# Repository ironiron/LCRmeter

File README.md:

# About

My try at LCR measurment via sinewave and voltage measurment. Generally, it is working, however PCB layout is not great, and ADC is not used optymally, so measuring inductance is more or less futile.
Results are a bit floaty. There is an unpolished oscilloscope mode.

Seems like PCB needs a bit of rerouting.

# Measuring principle. 

See \ref misc folder for more in depth walkthrough. The principle is to measure voltage across known resistor and a DUT.
Since it is sinewave that is used for measurments we can get phase angle, loss angle, etc. 

Now measurment settings (frequency and series resistor), are done manually, but maybe implement automatic one in the future?
eg. if loss angle is small then the capacitance can be calculated with greater accuracy than the ESR. If inductor is to be measured then the measuring frequency should be higher. 

# TODO 

- add under sampling on ADC to increase range of frequency for sinewave
- Add automatic frequency and Rseries adjustment for best possible accuracy.
- reroute PCB
- Add edge detection for oscilloscope mode
- add handling of arbitrary waveform and PWM outputs
- Remove USB stuff - not needed
-

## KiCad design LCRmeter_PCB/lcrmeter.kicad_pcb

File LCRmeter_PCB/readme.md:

# todo

[x] add connector for UART converter for debugging
[x] add testpoint for ADC measurments
[x] make oled from discrete parts, not module
[x] change connector for programmmer, and move it out of the top layer
- check if PCB can be smaller (especially batterry holder)
[x] add more Rseries options
[x] remove option without Rseries connected at all - it can fry PCB
[x] remove connection to 2nd ADCs
[x] Are there  better opamps?? 
[x] remove option for 1.5 V ref
[x] reduce number of caps, and increase its capacitance
[x] think about Rseries diagnosis
[x] make programming interface coherent with stlink or make something with proper connnection
- think about connections to from MCU 
[x] is there MCU with bigger RAM? (no there is none in g4 series)
[] add pulldown for the reset of oled
[] add mounting points for mechanical assembly
- double check connections on schematic

# Decisions background

74LVC1G66 Switches needs to be placed before Rseries so that ADC measurments do no take into account resistance of switches itself.

PCB should be 4 layer to improve EMC. Inner layers should be GND only, VCC is not so critical that needs a power plane.

Capacitors should be 0603 or lower

R series will not have any self diagnosis - too much hassle for little added accuracy

Filters are designed using Analog Devices tool  (https://tools.analog.com/en/filterwizard/)[https://tools.analog.com/en/filterwizard/]
![[media/filters.png]]
Requirments for filter is that 125KHz is a passband with optimally 0 dB ripples and no gain. Alternatively a simple RC filter can be used. Because ADC takes is too invasive for the signal (sampling period is cleary visible on osciloscope), at least internal op-amp is required.

Capacitors for uC are set to larger for same size, in the hope of improving noise performance. There is no simulation done for either option (many little plus one big, vs many bigger), so I do not know if it works, but there is no indication that either is better than other. ST's guidelines seems to be so called tradition of caps of 3 diffferent values.

Copper pour on top and bottom is not allowed, because it can create easi to overlook noisy cavities.

ADCs are on pins that can be mapped thru internal opamp

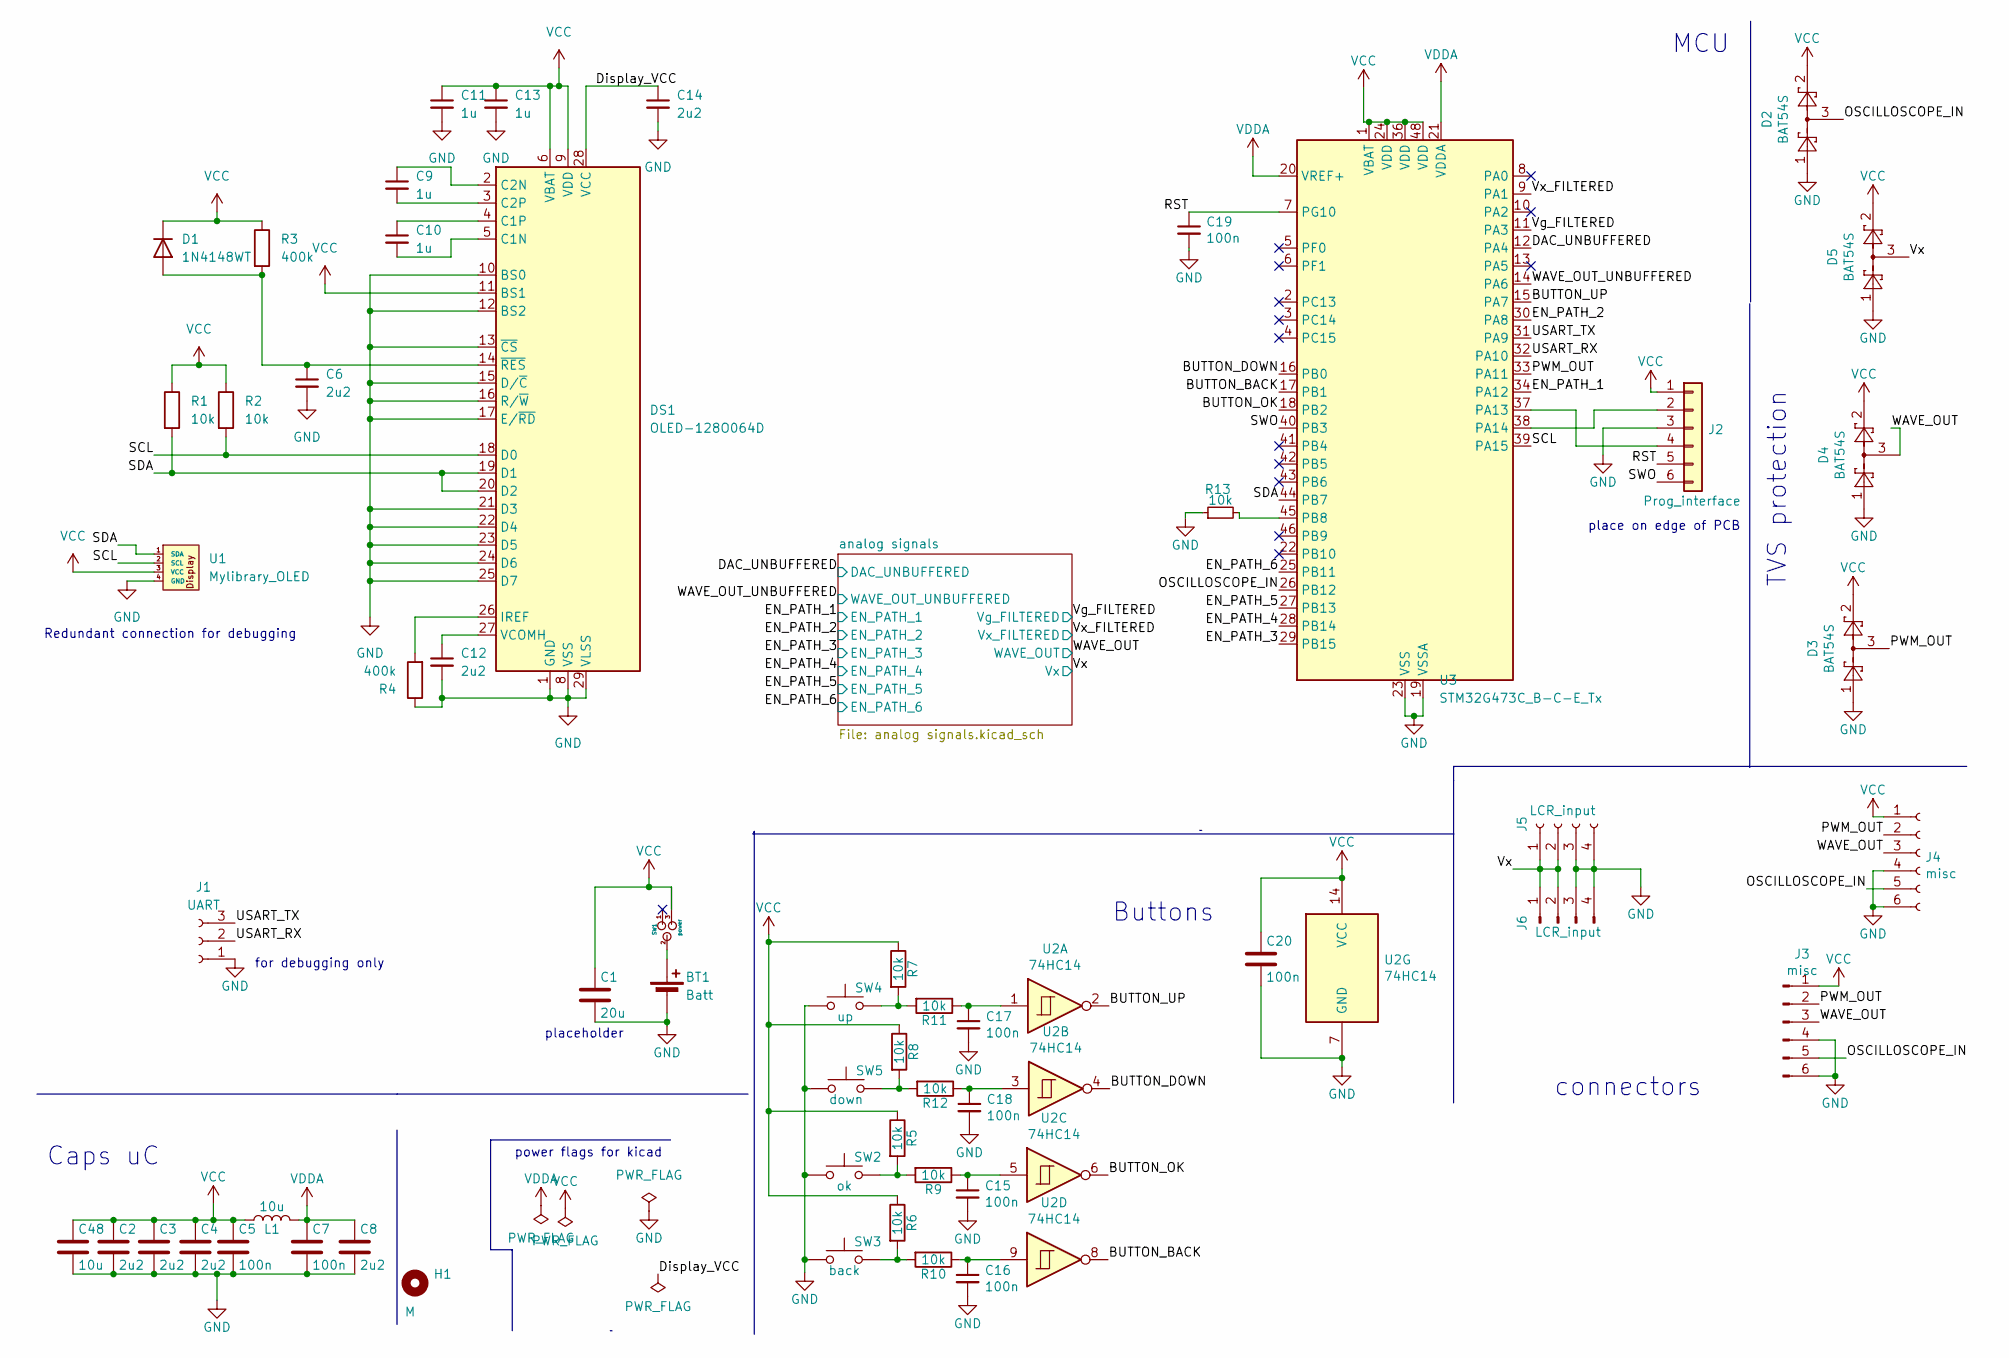
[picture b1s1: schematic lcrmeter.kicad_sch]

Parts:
BT1: Batt; BatteryHolder_Keystone_2468_2xAAA
C1: 20u; C_0805_2012Metric_Pad1.18x1.45mm_HandSolder
C2, C3, C4, C6, C8, C12, C14: 2u2; C_0402_1005Metric_Pad0.74x0.62mm_HandSolder
C5, C7, C15, C16, C17, C18, C19, C20: 100n; C_0402_1005Metric_Pad0.74x0.62mm_HandSolder
C9, C10, C11, C13: 1u; C_0402_1005Metric_Pad0.74x0.62mm_HandSolder
C48: 10u; C_0805_2012Metric_Pad1.18x1.45mm_HandSolder
D1: 1N4148WT; D_SOD-523
D2, D3, D4, D5: BAT54S; SOT-23
DS1: OLED-128O064D
H1: M; MountingHole_3.2mm_M3_ISO14580
J1: UART; Harwin_M20-89003xx_1x03_P2.54mm_Horizontal
J2: Prog_interface; Harwin_M20-89006xx_1x06_P2.54mm_Horizontal
J3: misc; PinSocket_1x06_P2.54mm_Vertical
J4: misc; PinHeader_1x06_P2.54mm_Vertical
J5: LCR_input; PinSocket_1x04_P2.54mm_Vertical
J6: LCR_input; PinHeader_1x04_P2.54mm_Vertical
L1: 10u; L_0805_2012Metric_Pad1.15x1.40mm_HandSolder
R1, R2, R5, R6, R7, R8, R9, R10, R11, R12, R13: 10k; R_0603_1608Metric_Pad0.98x0.95mm_HandSolder
R3, R4: 400k; R_0603_1608Metric_Pad0.98x0.95mm_HandSolder
SW1: power; PinHeader_1x03_P2.54mm_Vertical
SW2: ok; SW_SPST_REED_CT05-XXXX-G1
SW3: back; SW_SPST_REED_CT05-XXXX-G1
SW4: up; SW_SPST_REED_CT05-XXXX-G1
SW5: down; SW_SPST_REED_CT05-XXXX-G1
U1: Mylibrary_OLED; PinHeader_1x04_P2.54mm_Vertical
U2: 74HC14; SOIC-14_3.9x8.7mm_P1.27mm
U3: STM32G473C_B-C-E_Tx; LQFP-48_7x7mm_P0.5mm

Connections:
/BUTTON_BACK: U2.8, U3.17 (PB1)
/BUTTON_DOWN: U2.4, U3.16 (PB0)
/BUTTON_OK: U2.6, U3.18 (PB2)
/BUTTON_UP: U2.2, U3.15 (PA7)
/DAC_UNBUFFERED: U3.12 (PA4); also elsewhere on the board
/Display_VCC: C14.1, DS1.28 (VCC)
/EN_PATH_1: U3.34 (PA12); also elsewhere on the board
/EN_PATH_2: U3.30 (PA8); also elsewhere on the board
/EN_PATH_3: U3.29 (PB15); also elsewhere on the board
/EN_PATH_4: U3.28 (PB14); also elsewhere on the board
/EN_PATH_5: U3.27 (PB13); also elsewhere on the board
/EN_PATH_6: U3.25 (PB11); also elsewhere on the board
/OSCILLOSCOPE_IN: D2.3, J3.5, J4.5, U3.26 (PB12)
/PWM_OUT: D3.3, J3.2, J4.2, U3.33 (PA11)
/RST: C19.1, J2.5, U3.7 (PG10)
/SCL: DS1.18 (D0), R2.2, U1.2 (SCL), U3.39 (PA15)
/SDA: DS1.19 (D1), DS1.20 (D2), R1.2, U1.1 (SDA), U3.44 (PB7)
/SWO: J2.6, U3.40 (PB3)
/USART_RX: J1.2, U3.32 (PA10)
/USART_TX: J1.3, U3.31 (PA9)
/Vg_FILTERED: U3.11 (PA3); also elsewhere on the board
/Vx: D5.3, J5.1, J5.2, J6.1, J6.2; also elsewhere on the board
/Vx_FILTERED: U3.9 (PA1); also elsewhere on the board
/WAVE_OUT: D4.3, J3.3, J4.3; also elsewhere on the board
/WAVE_OUT_UNBUFFERED: U3.14 (PA6); also elsewhere on the board
GND: BT1.2 (-), C1.2, C2.2, C3.2, C4.2, C5.2, C6.2, C7.2, C8.2, C11.2, C12.2, C13.2, C14.2, C15.2, C16.2, C17.2, C18.2, C19.2, C20.2, C48.2, D2.1, D3.1, D4.1, D5.1, DS1.1 (GND), DS1.8 (VSS), DS1.10 (BS0), DS1.12 (BS2), DS1.13 (~CS), DS1.15 (D/~C), DS1.16 (R/~W), DS1.17 (E/~RD), DS1.21 (D3), DS1.22 (D4), DS1.23 (D5), DS1.24 (D6), DS1.25 (D7), DS1.29 (VLSS), DS1.30 (GND), J1.1, J2.3, J3.4, J3.6, J4.4, J4.6, J5.3, J5.4, J6.3, J6.4, R4.1, R13.1, SW2.1, SW3.1, SW4.1, SW5.1, U1.4 (GND), U2.7 (GND), U3.19 (VSSA), U3.23 (VSS), U3.35 (VSS), U3.47 (VSS); also elsewhere on the board
unnamed: BT1.1 (+), SW1.2
unnamed: C15.1, R9.1, U2.5
unnamed: C16.1, R10.1, U2.9
unnamed: C17.1, R11.1, U2.1
unnamed: C18.1, R12.1, U2.3
unnamed: C6.1, D1.2 (A), DS1.14 (~RES), R3.2
unnamed: C10.2, DS1.5 (C1N)
unnamed: C10.1, DS1.4 (C1P)
unnamed: C9.1, DS1.2 (C2N)
unnamed: C9.2, DS1.3 (C2P)
unnamed: DS1.26 (IREF), R4.2
unnamed: C12.1, DS1.27 (VCOMH)
unnamed: J2.2, U3.38 (PA14)
unnamed: J2.4, U3.37 (PA13)
unnamed: R5.2, R9.2, SW2.2
unnamed: R6.2, R10.2, SW3.2
unnamed: R7.2, R11.2, SW4.2
unnamed: R8.2, R12.2, SW5.2
unnamed: R13.2, U3.45 (PB8)
VCC: C1.1, C2.1, C3.1, C4.1, C5.1, C11.1, C13.1, C20.1, C48.1, D1.1 (K), D2.2, D3.2, D4.2, D5.2, DS1.6 (VBAT), DS1.9 (VDD), DS1.11 (BS1), J2.1, J3.1, J4.1, L1.1, R1.1, R2.1, R3.1, R5.1, R6.1, R7.1, R8.1, SW1.3, U1.3 (VCC), U2.14 (VCC), U3.1 (VBAT), U3.24 (VDD), U3.36 (VDD), U3.48 (VDD); also elsewhere on the board
VDDA: C7.1, C8.1, L1.2, U3.20 (VREF+), U3.21 (VDDA)

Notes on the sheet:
placeholder
Redundant connection for debugging
place on edge of PCB
Buttons
for debugging only
TVS protection
connectors
power flags for kicad
Caps uC
MCU

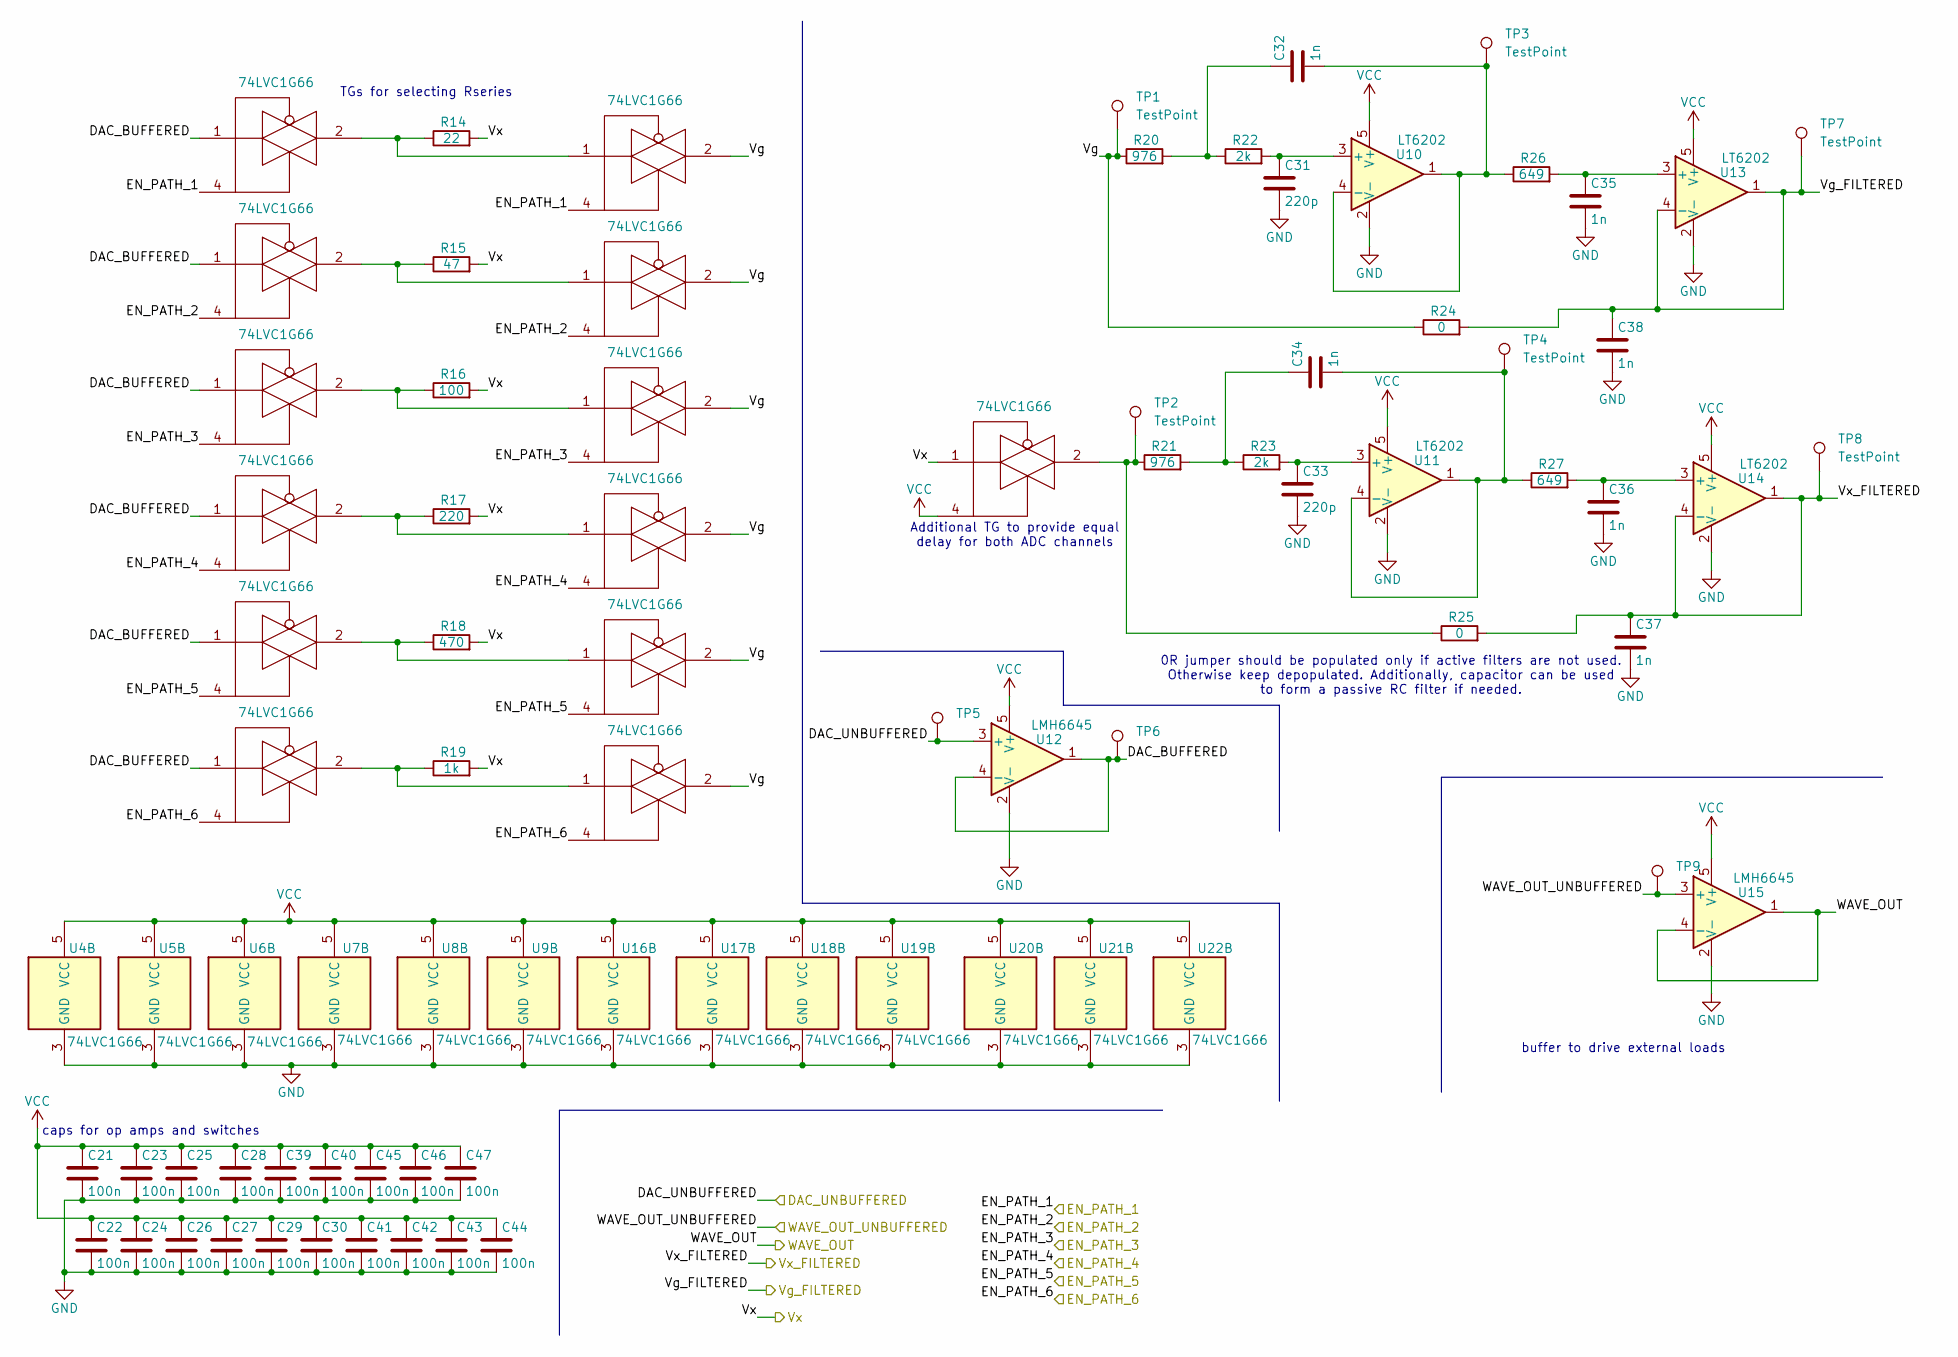
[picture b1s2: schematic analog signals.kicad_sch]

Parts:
C21, C22, C23, C24, C25, C26, C27, C28, C29, C30, C39, C40, C41, C42, C43, C44, C45, C46, C47: 100n; C_0402_1005Metric_Pad0.74x0.62mm_HandSolder
C31, C33: 220p; C_0402_1005Metric_Pad0.74x0.62mm_HandSolder
C32, C34, C35, C36, C37, C38: 1n; C_0402_1005Metric_Pad0.74x0.62mm_HandSolder
R14: 22; R_0603_1608Metric_Pad0.98x0.95mm_HandSolder
R15: 47; R_0603_1608Metric_Pad0.98x0.95mm_HandSolder
R16: 100; R_0603_1608Metric_Pad0.98x0.95mm_HandSolder
R17: 220; R_0603_1608Metric_Pad0.98x0.95mm_HandSolder
R18: 470; R_0603_1608Metric_Pad0.98x0.95mm_HandSolder
R19: 1k; R_0603_1608Metric_Pad0.98x0.95mm_HandSolder
R20, R21: 976; R_0603_1608Metric_Pad0.98x0.95mm_HandSolder
R22, R23: 2k; R_0603_1608Metric_Pad0.98x0.95mm_HandSolder
R24, R25: 0; R_0603_1608Metric_Pad0.98x0.95mm_HandSolder
R26, R27: 649; R_0603_1608Metric_Pad0.98x0.95mm_HandSolder
TP1, TP2, TP3, TP4, TP7, TP8: TestPoint; TestPoint_Pad_D1.5mm
TP5, TP6, TP9: TestPoint_Pad_D1.5mm
U4, U5, U6, U7, U8, U9, U16, U17, U18, U19, U20, U21, U22: 74LVC1G66; SOT-23-5
U10, U11, U13, U14: LT6202; SOT-23-5
U12, U15: LMH6645; SOT-23-5

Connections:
/DAC_UNBUFFERED: TP5.1, U12.3 (+); also elsewhere on the board
/EN_PATH_1: U6.4, U16.4; also elsewhere on the board
/EN_PATH_2: U7.4, U17.4; also elsewhere on the board
/EN_PATH_3: U5.4, U18.4; also elsewhere on the board
/EN_PATH_4: U8.4, U19.4; also elsewhere on the board
/EN_PATH_5: U9.4, U20.4; also elsewhere on the board
/EN_PATH_6: U4.4, U21.4; also elsewhere on the board
/Vg_FILTERED: C38.1, R24.2, TP7.1, U13.1, U13.4 (-); also elsewhere on the board
/Vx: R14.2, R15.2, R16.2, R17.2, R18.2, R19.2, U22.1; also elsewhere on the board
/Vx_FILTERED: C37.1, R25.2, TP8.1, U14.1, U14.4 (-); also elsewhere on the board
/WAVE_OUT: U15.1, U15.4 (-); also elsewhere on the board
/WAVE_OUT_UNBUFFERED: TP9.1, U15.3 (+); also elsewhere on the board
/analog signals/DAC_BUFFERED: TP6.1, U4.1, U5.1, U6.1, U7.1, U8.1, U9.1, U12.1, U12.4 (-)
/analog signals/Vg: R20.1, R24.1, TP1.1, U16.2, U17.2, U18.2, U19.2, U20.2, U21.2
GND: C21.2, C22.2, C23.2, C24.2, C25.2, C26.2, C27.2, C28.2, C29.2, C30.2, C31.2, C33.2, C35.2, C36.2, C37.2, C38.2, C39.2, C40.2, C41.2, C42.2, C43.2, C44.2, C45.2, C46.2, C47.2, U4.3 (GND), U5.3 (GND), U6.3 (GND), U7.3 (GND), U8.3 (GND), U9.3 (GND), U10.2 (V-), U11.2 (V-), U12.2 (V-), U13.2 (V-), U14.2 (V-), U15.2 (V-), U16.3 (GND), U17.3 (GND), U18.3 (GND), U19.3 (GND), U20.3 (GND), U21.3 (GND), U22.3 (GND); also elsewhere on the board
unnamed: C32.1, R20.2, R22.1
unnamed: C34.1, R21.2, R23.1
unnamed: R14.1, U6.2, U16.1
unnamed: R15.1, U7.2, U17.1
unnamed: R16.1, U5.2, U18.1
unnamed: R17.1, U8.2, U19.1
unnamed: R18.1, U9.2, U20.1
unnamed: R19.1, U4.2, U21.1
unnamed: R21.1, R25.1, TP2.1, U22.2
unnamed: C31.1, R22.2, U10.3 (+)
unnamed: C32.2, R26.1, TP3.1, U10.1, U10.4 (-)
unnamed: C33.1, R23.2, U11.3 (+)
unnamed: C34.2, R27.1, TP4.1, U11.1, U11.4 (-)
unnamed: C35.1, R26.2, U13.3 (+)
unnamed: C36.1, R27.2, U14.3 (+)
VCC: C21.1, C22.1, C23.1, C24.1, C25.1, C26.1, C27.1, C28.1, C29.1, C30.1, C39.1, C40.1, C41.1, C42.1, C43.1, C44.1, C45.1, C46.1, C47.1, U4.5 (VCC), U5.5 (VCC), U6.5 (VCC), U7.5 (VCC), U8.5 (VCC), U9.5 (VCC), U10.5 (V+), U11.5 (V+), U12.5 (V+), U13.5 (V+), U14.5 (V+), U15.5 (V+), U16.5 (VCC), U17.5 (VCC), U18.5 (VCC), U19.5 (VCC), U20.5 (VCC), U21.5 (VCC), U22.4, U22.5 (VCC); also elsewhere on the board

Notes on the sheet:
Additional TG to provide equal delay for both ADC channels
TGs for selecting Rseries
0R jumper should be populated only if active filters are not used. Otherwise keep depopulated. Additionally, capacitor can be used to form a passive RC filter if needed.
caps for op amps and switches
buffer to drive external loads

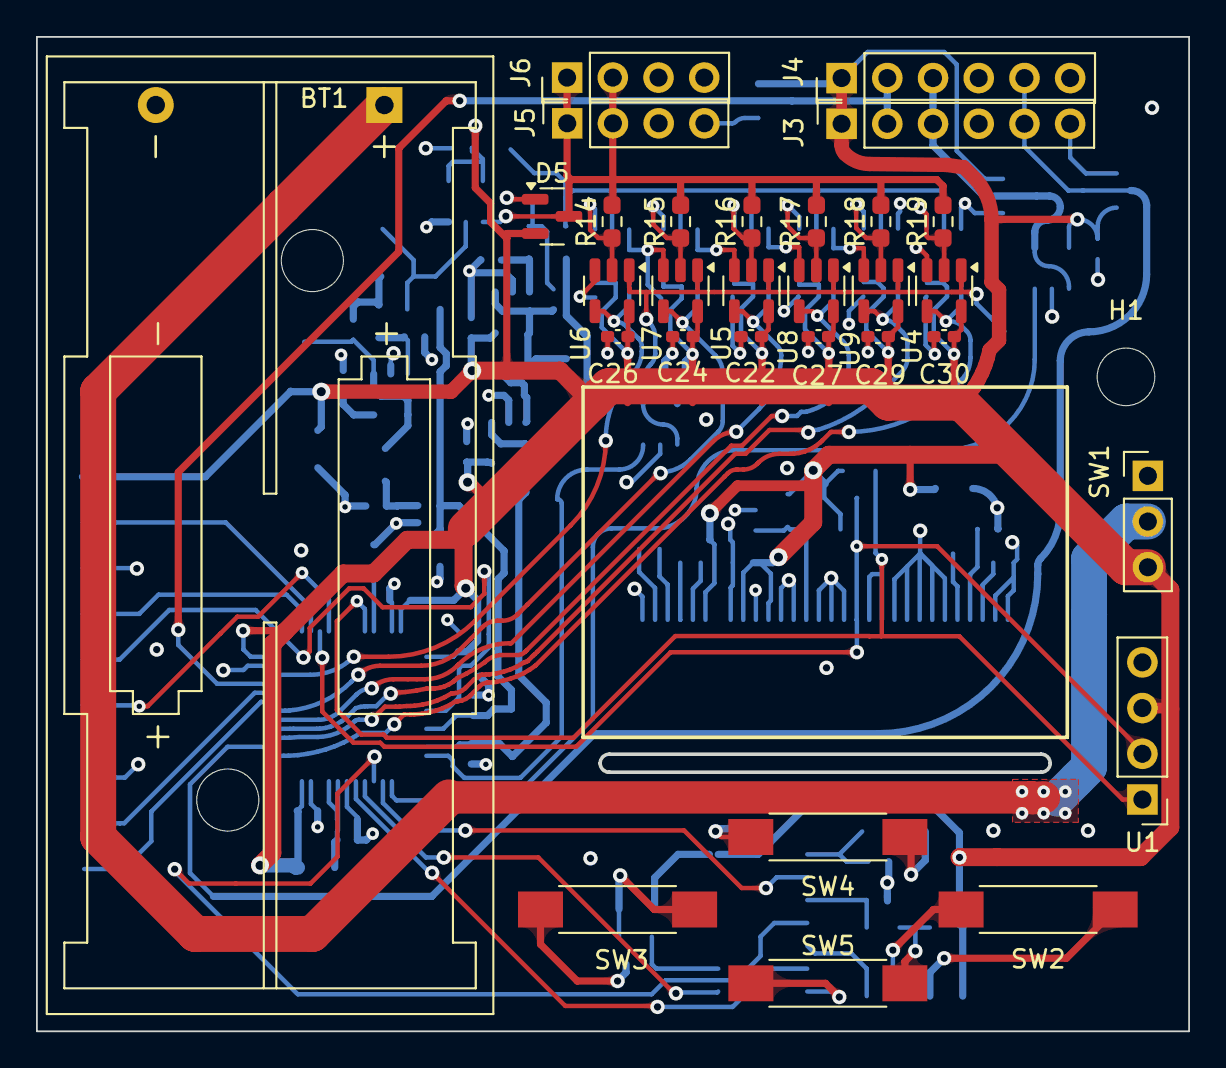
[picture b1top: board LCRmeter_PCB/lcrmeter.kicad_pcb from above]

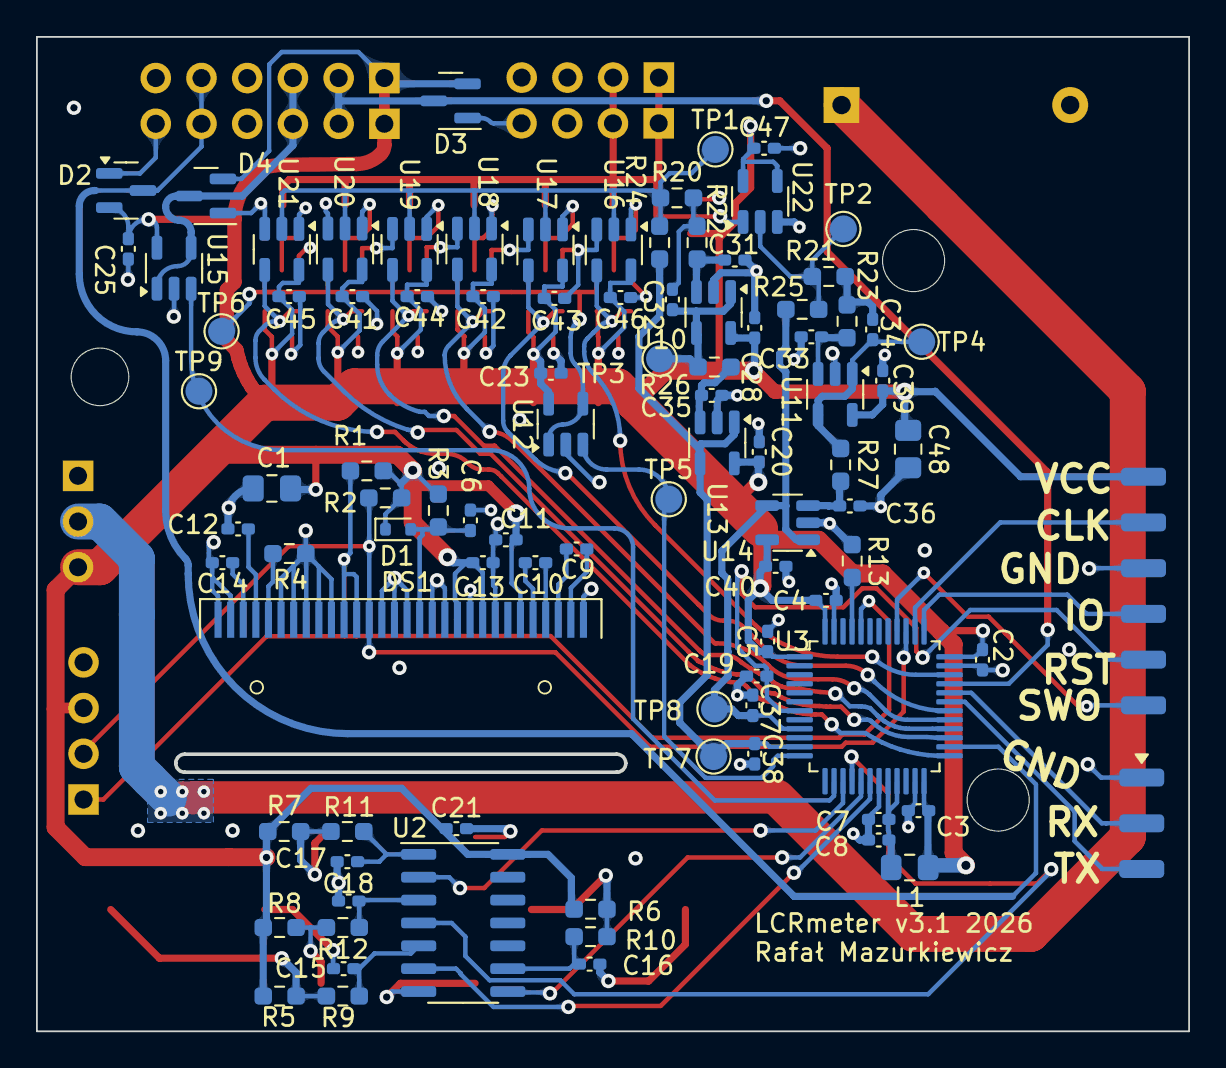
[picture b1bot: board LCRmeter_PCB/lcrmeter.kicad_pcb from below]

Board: 4 copper layers, 64.0 x 55.2 mm, 126 parts (95 on the bottom side), 64 nets.

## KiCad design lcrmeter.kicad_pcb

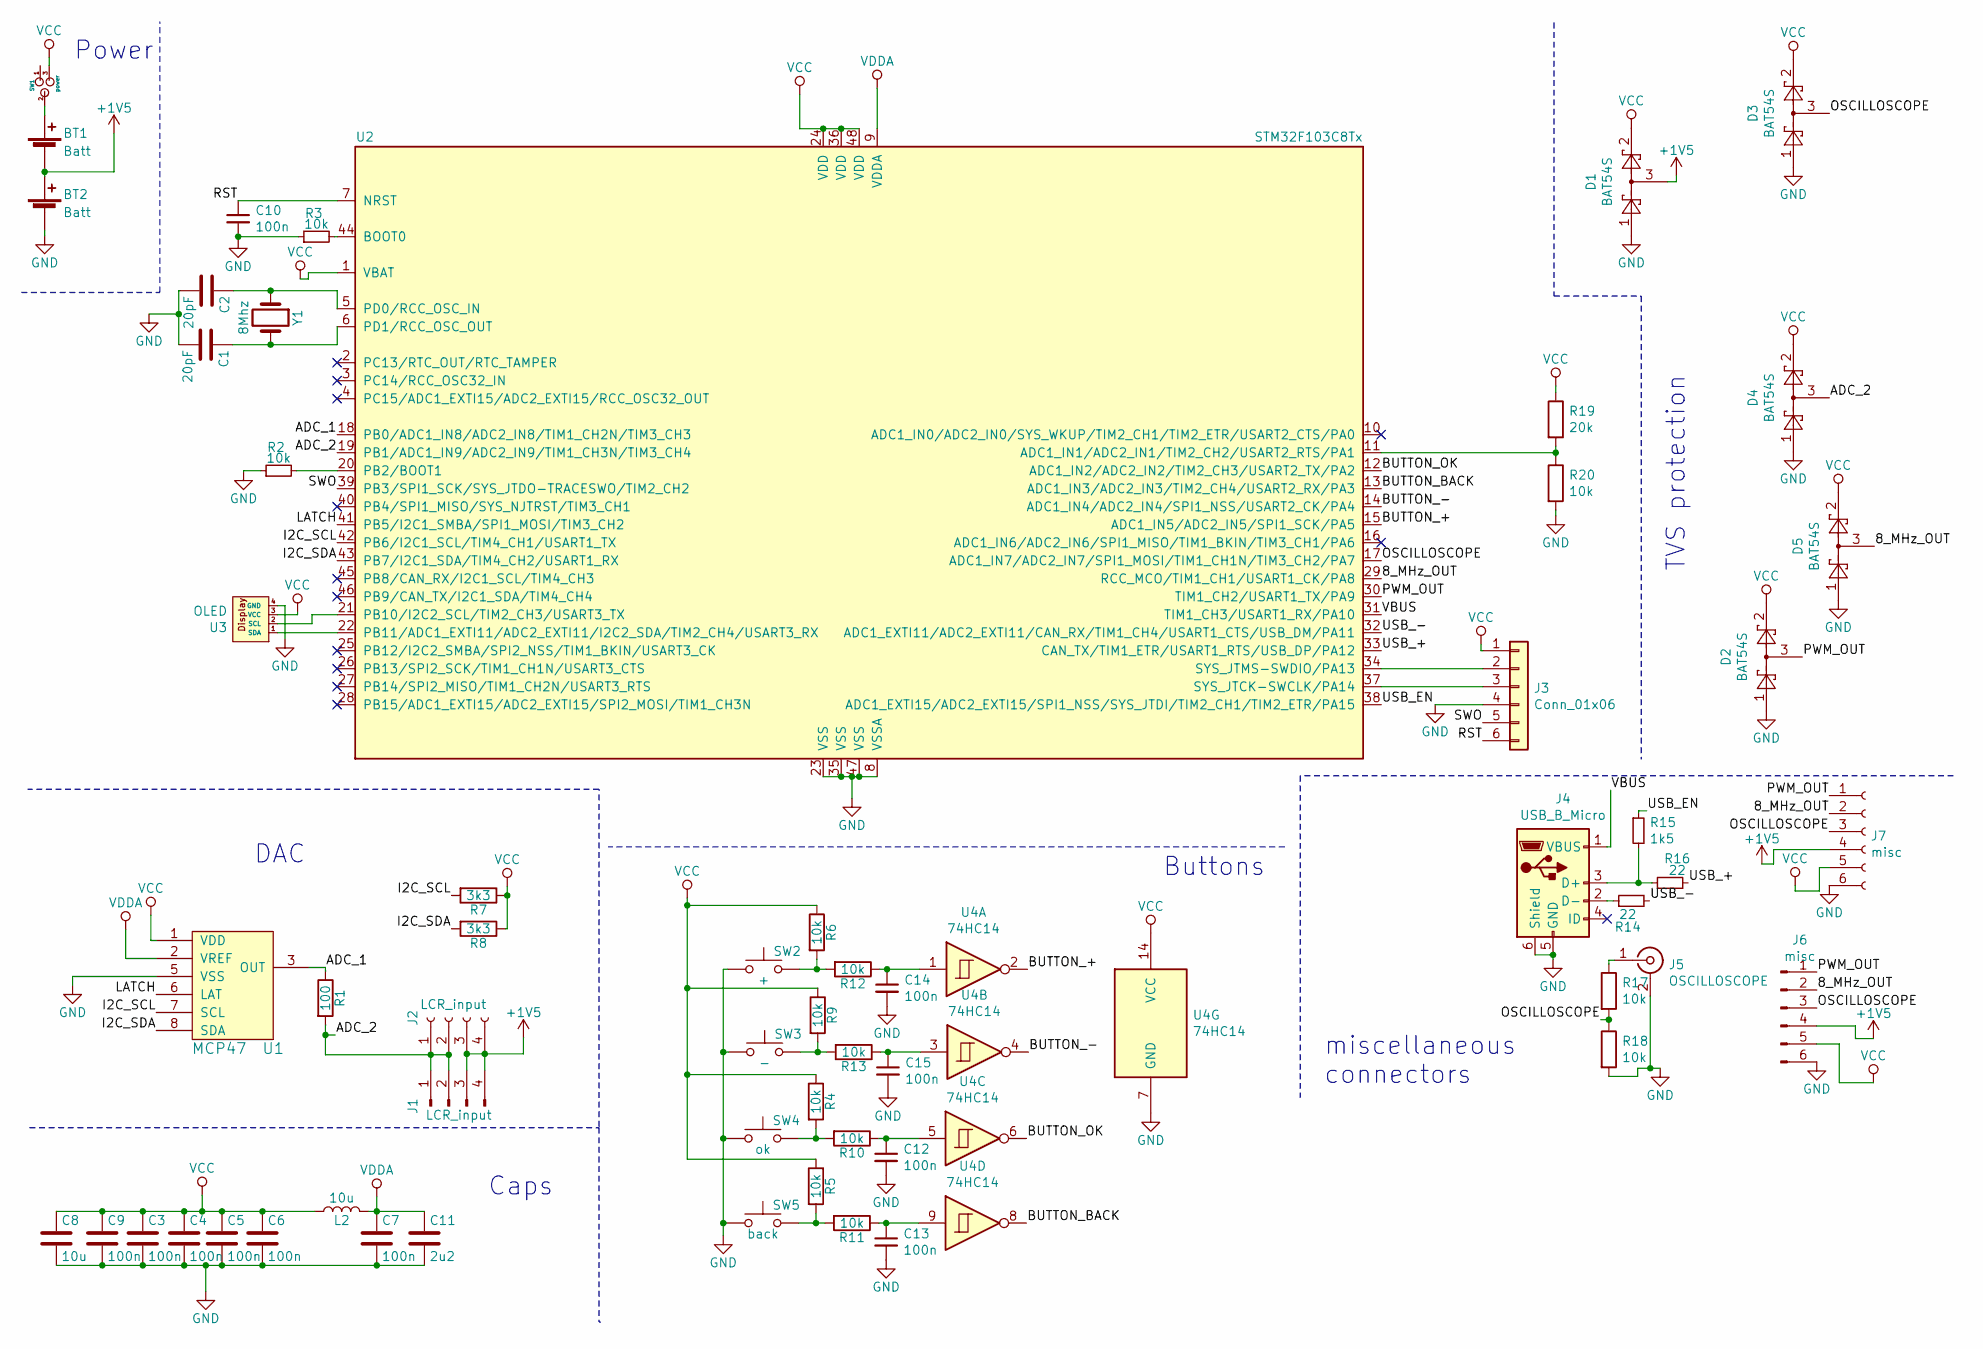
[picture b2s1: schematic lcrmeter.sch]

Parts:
BT1, BT2: Batt; BatteryHolder_Keystone_2466_1xAAA
C1, C2: 20pF; C_0805_2012Metric_Pad1.15x1.40mm_HandSolder
C3, C4, C5, C6, C7, C9, C10, C12, C13, C14, C15: 100n; C_0603_1608Metric_Pad1.05x0.95mm_HandSolder
C8: 10u; C_0603_1608Metric_Pad1.05x0.95mm_HandSolder
C11: 2u2; C_0805_2012Metric_Pad1.15x1.40mm_HandSolder
D1, D2, D3, D4, D5: BAT54S; SOT-23
J1: LCR_input; PinHeader_1x04_P2.54mm_Vertical
J2: LCR_input; PinSocket_1x04_P2.54mm_Vertical
J3: Conn_01x06; PinHeader_1x06_P2.54mm_Vertical
J4: USB_B_Micro; USB_Micro-B_Molex_47346-0001
J5: OSCILLOSCOPE; BNC TE CONNECTIVITY 5-1634503
J6: misc; PinSocket_1x06_P2.54mm_Vertical
J7: misc; PinHeader_1x06_P2.54mm_Vertical
L2: 10u; L_0805_2012Metric_Pad1.15x1.40mm_HandSolder
R1: 100; R_0805_2012Metric_Pad1.15x1.40mm_HandSolder
R2, R3, R4, R5, R6, R9, R10, R11, R12, R13, R17, R18, R20: 10k; R_0603_1608Metric_Pad1.05x0.95mm_HandSolder
R7, R8: 3k3; R_0805_2012Metric_Pad1.15x1.40mm_HandSolder
R14, R16: 22; R_0805_2012Metric_Pad1.15x1.40mm_HandSolder
R15: 1k5; R_0805_2012Metric_Pad1.15x1.40mm_HandSolder
R19: 20k; R_0805_2012Metric_Pad1.15x1.40mm_HandSolder
SW1: power; PinHeader_1x03_P2.54mm_Vertical
SW2: +; SW_SPST_REED_CT05-XXXX-G1
SW3: -; SW_SPST_REED_CT05-XXXX-G1
SW4: ok; SW_SPST_REED_CT05-XXXX-G1
SW5: back; SW_SPST_REED_CT05-XXXX-G1
U1: MCP47; TSSOP-8_4.4x3mm_P0.65mm
U2: STM32F103C8Tx; LQFP-48_7x7mm_P0.5mm
U3: OLED; OLED_128x64
U4: 74HC14; SOIC-14_3.9x8.7mm_P1.27mm
Y1: 8Mhz; Crystal_HC49-U_Vertical

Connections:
/8_MHz_OUT: D5.3, J6.2, J7.2, U2.29 (RCC_MCO/TIM1_CH1/USART1_CK/PA8)
/ADC_1: R1.1, U1.3 (OUT), U2.18 (PB0/ADC1_IN8/ADC2_IN8/TIM1_CH2N/TIM3_CH3)
/ADC_2: D4.3, J1.1, J1.2, J2.1, J2.2, R1.2, U2.19 (PB1/ADC1_IN9/ADC2_IN9/TIM1_CH3N/TIM3_CH4)
/BUTTON_+: U2.15 (ADC1_IN5/ADC2_IN5/SPI1_SCK/PA5), U4.2
/BUTTON_-: U2.14 (ADC1_IN4/ADC2_IN4/SPI1_NSS/USART2_CK/PA4), U4.4
/BUTTON_BACK: U2.13 (ADC1_IN3/ADC2_IN3/TIM2_CH4/USART2_RX/PA3), U4.8
/BUTTON_OK: U2.12 (ADC1_IN2/ADC2_IN2/TIM2_CH3/USART2_TX/PA2), U4.6
/I2C_SCL: R7.2, U1.7 (SCL), U2.42 (PB6/I2C1_SCL/TIM4_CH1/USART1_TX)
/I2C_SDA: R8.2, U1.8 (SDA), U2.43 (PB7/I2C1_SDA/TIM4_CH2/USART1_RX)
/LATCH: U1.6 (LAT), U2.41 (PB5/I2C1_SMBA/SPI1_MOSI/TIM3_CH2)
/OSCILLOSCOPE: D3.3, J6.3, J7.3, R17.2, R18.1, U2.17 (ADC1_IN7/ADC2_IN7/SPI1_MOSI/TIM1_CH1N/T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)
/PWM_OUT: D2.3, J6.1, J7.1, U2.30 (TIM1_CH2/USART1_TX/PA9)
/RST: C10.1, J3.6, U2.7 (NRST)
/SWO: J3.5, U2.39 (PB3/SPI1_SCK/SYS_JTDO-TRACESWO/TIM2_CH2)
/USB_+: R16.2, U2.33 (CAN_TX/TIM1_ETR/USART1_RTS/USB_DP/PA12)
/USB_-: R14.2, U2.32 (ADC1_EXTI11/ADC2_EXTI11/CAN_RX/TIM1_CH4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)
/USB_EN: R15.1, U2.38 (ADC1_EXTI15/ADC2_EXTI15/SPI1_NSS/SYS_JT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)
/VBUS: J4.1 (VBUS), U2.31 (TIM1_CH3/USART1_RX/PA10)
GND: BT2.2 (-), C1.2, C2.2, C3.2, C4.2, C5.2, C6.2, C7.2, C8.2, C9.2, C10.2, C11.2, C12.2, C13.2, C14.2, C15.2, D1.1, D2.1, D3.1, D4.1, D5.1, J3.4, J4.5 (GND), J4.6 (Shield), J5.2 (Ext), J6.6, J7.6, R2.1, R3.1, R18.2, R20.2, SW2.1, SW3.1, SW4.1, SW5.1, U1.5 (VSS), U2.8 (VSSA), U2.23 (VSS), U2.35 (VSS), U2.47 (VSS), U3.4 (GND), U4.7 (GND); also elsewhere on the board
unnamed: BT1.1 (+), SW1.2
unnamed: C1.1, U2.6 (PD1/RCC_OSC_OUT), Y1.2
unnamed: C2.1, U2.5 (PD0/RCC_OSC_IN), Y1.1
unnamed: C12.1, R10.1, U4.5
unnamed: C13.1, R11.1, U4.9
unnamed: C14.1, R12.1, U4.1
unnamed: C15.1, R13.1, U4.3
unnamed: J3.2, U2.34 (SYS_JTMS-SWDIO/PA13)
unnamed: J3.3, U2.37 (SYS_JTCK-SWCLK/PA14)
unnamed: J4.2 (D-), R14.1
unnamed: J4.3 (D+), R15.2, R16.1
unnamed: J5.1 (In), R17.1
unnamed: R2.2, U2.20 (PB2/BOOT1)
unnamed: R3.2, U2.44 (BOOT0)
unnamed: R4.2, R10.2, SW4.2
unnamed: R5.2, R11.2, SW5.2
unnamed: R6.2, R12.2, SW2.2
unnamed: R9.2, R13.2, SW3.2
unnamed: R19.2, R20.1, U2.11 (ADC1_IN1/ADC2_IN1/TIM2_CH2/USART2_RTS/P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)
unnamed: U2.21 (PB10/I2C2_SCL/TIM2_CH3/USART3_TX), U3.2 (SCL)
unnamed: U2.22 (PB11/ADC1_EXTI11/ADC2_EXTI11/I2C2_SDA/T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), U3.1 (SDA)
VCC: C3.1, C4.1, C5.1, C6.1, C8.1, C9.1, D1.2, D2.2, D3.2, D4.2, D5.2, J3.1, J6.5, J7.5, L2.1, R4.1, R5.1, R6.1, R7.1, R8.1, R9.1, R19.1, SW1.3, U1.1 (VDD), U2.1 (VBAT), U2.24 (VDD), U2.36 (VDD), U2.48 (VDD), U3.3 (VCC), U4.14 (VCC); also elsewhere on the board
VDDA: C7.1, C11.1, L2.2, U1.2 (VREF), U2.9 (VDDA)

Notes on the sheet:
Buttons
miscellaneous connectors
TVS protection
DAC
Caps
Power

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
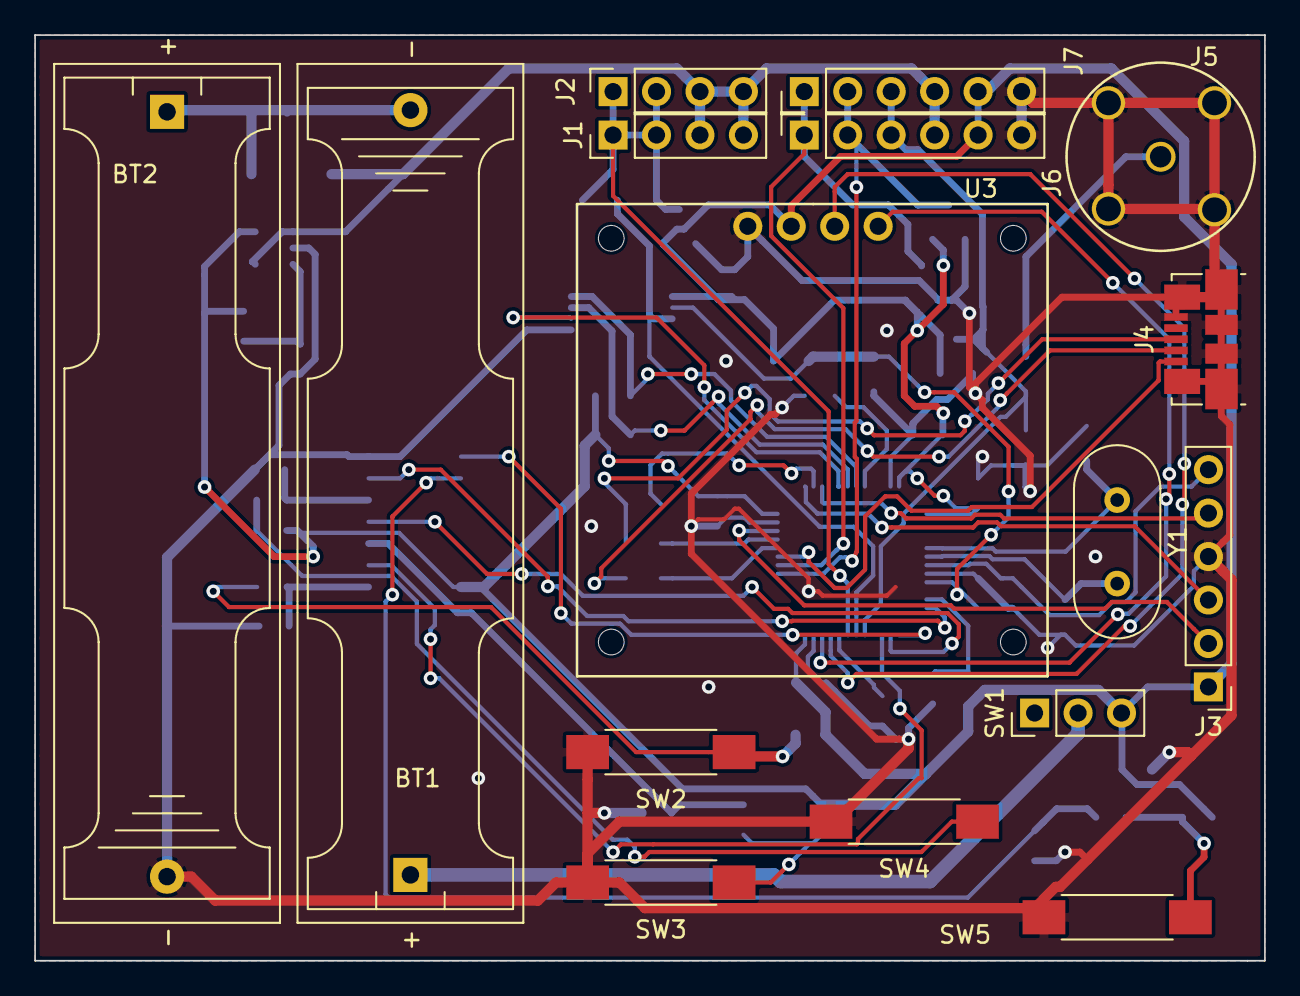
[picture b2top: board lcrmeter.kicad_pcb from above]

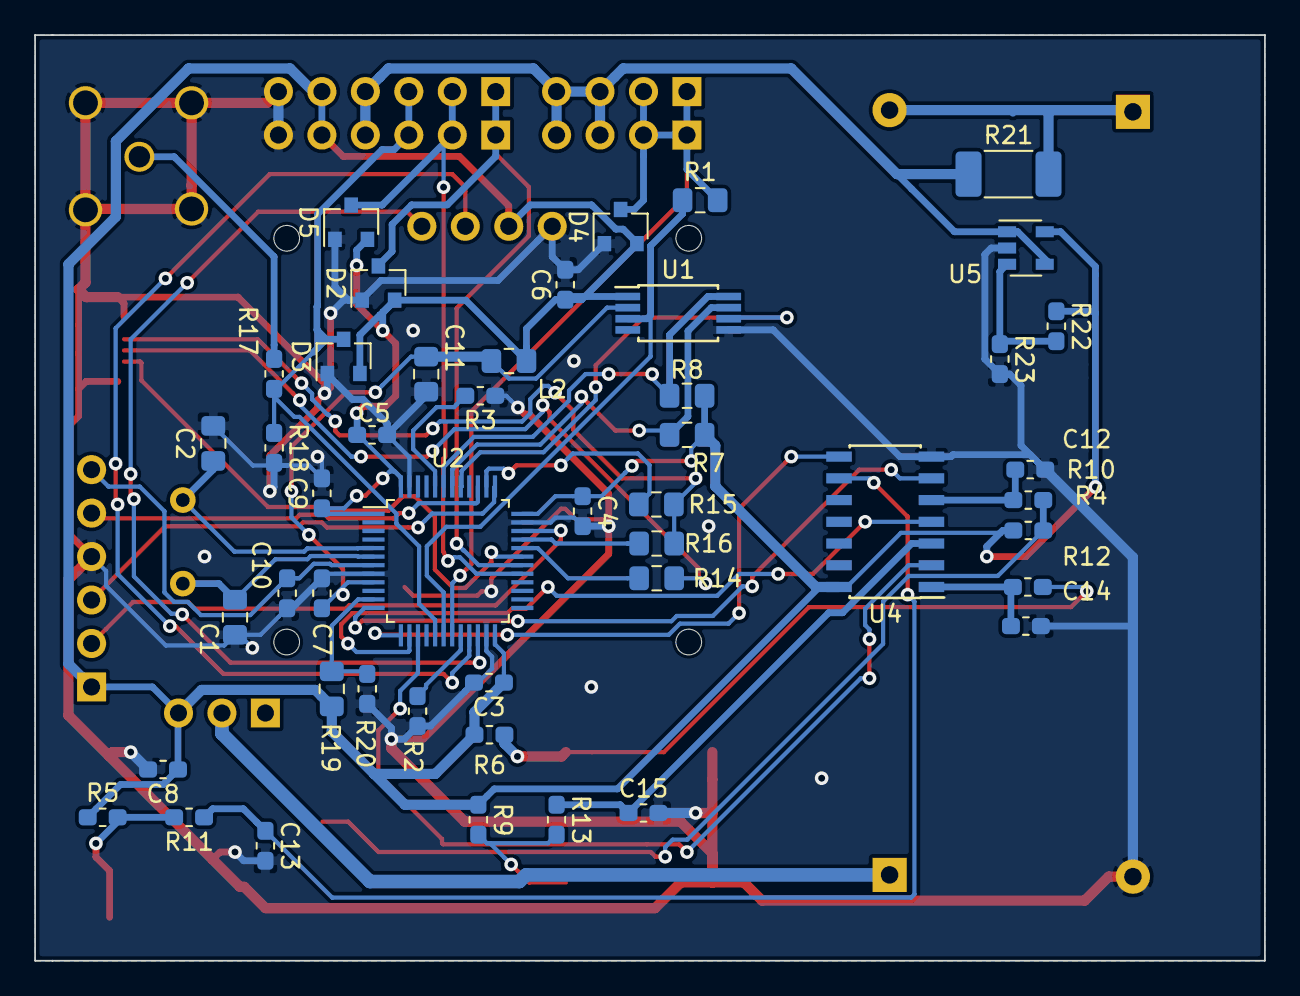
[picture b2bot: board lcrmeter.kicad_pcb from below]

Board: 2 copper layers, 71.9 x 54.1 mm, 63 parts (47 on the bottom side), 45 nets.

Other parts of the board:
R21: 0; R_2010_5025Metric_Pad1.52x2.65mm_HandSolder
R22, R23: 10k; R_0603_1608Metric_Pad1.05x0.95mm_HandSolder
U5: MCP6001-OT; SOT-23-5

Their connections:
GND: R23.2, U5.2; also elsewhere on the board
unnamed: R22.2, R23.1, U5.3
VCC: R22.1, U5.5; also elsewhere on the board
